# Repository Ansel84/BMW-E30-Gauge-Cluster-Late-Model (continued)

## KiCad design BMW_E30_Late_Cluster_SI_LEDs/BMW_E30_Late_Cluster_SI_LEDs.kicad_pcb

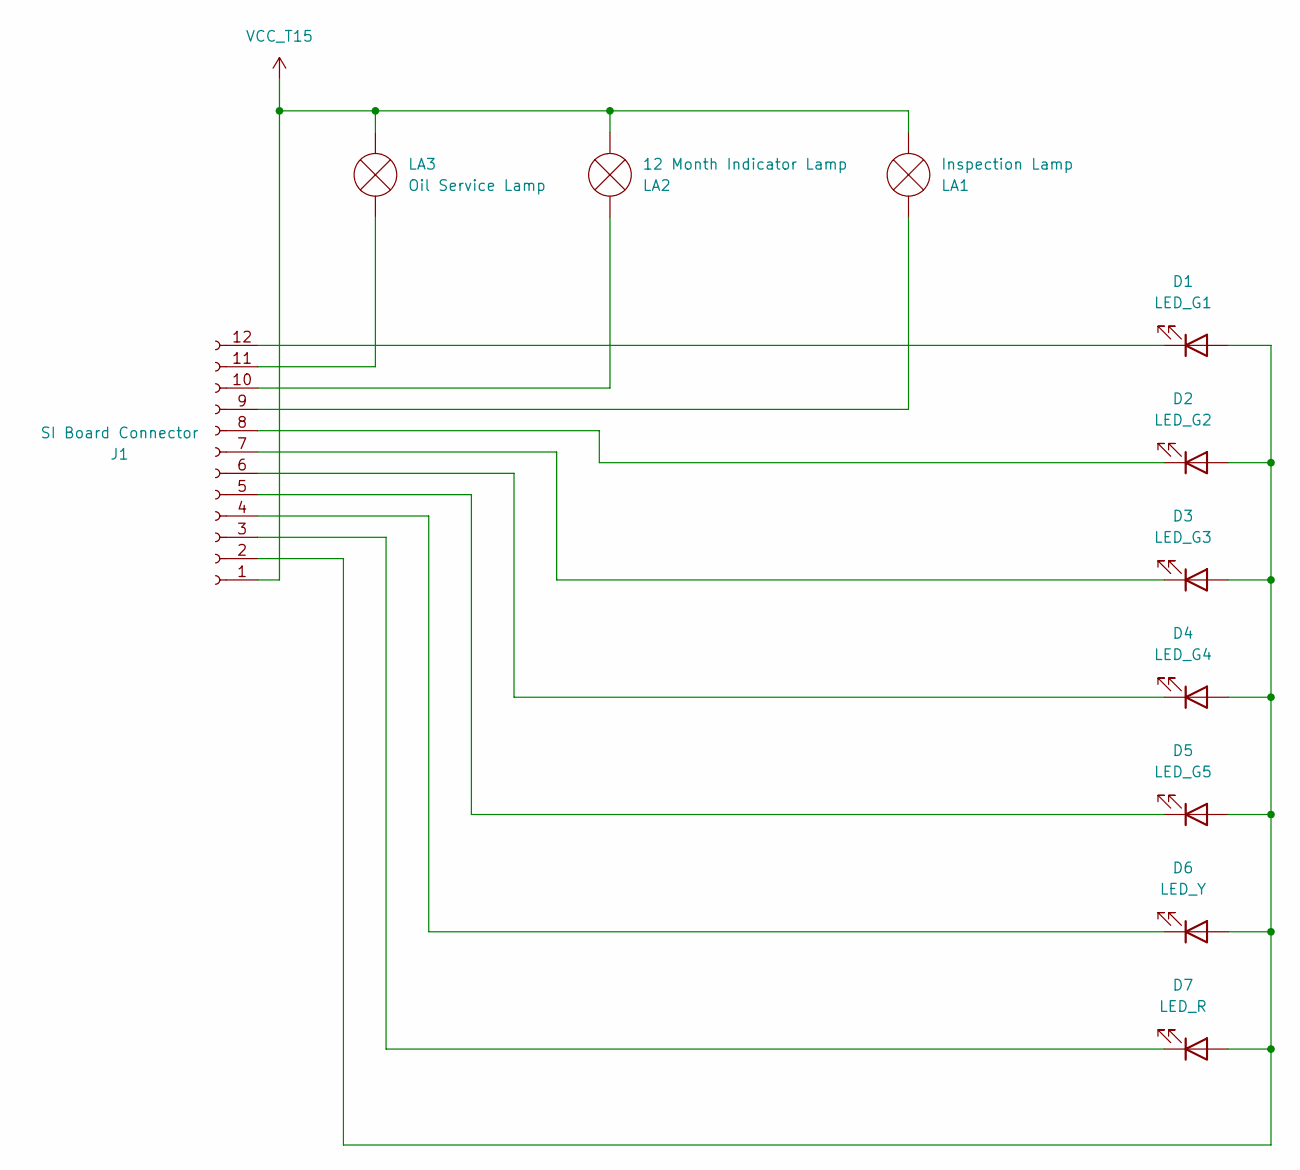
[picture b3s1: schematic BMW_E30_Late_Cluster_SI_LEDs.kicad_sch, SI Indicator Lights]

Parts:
D1: LED_G1; LED_D3.0mm
D2: LED_G2; LED_D3.0mm
D3: LED_G3; LED_D3.0mm
D4: LED_G4; LED_D3.0mm
D5: LED_G5; LED_D3.0mm
D6: LED_Y; LED_D3.0mm
D7: LED_R; LED_D3.0mm
J1: SI Board Connector; PinSocket_1x12_P2.54mm_Horizontal
LA1: Inspection Lamp; Lamp_D4.0mm_Horizontal_O3.81mm_Z2.0mm
LA2: 12 Month Indicator Lamp; Lamp_D4.0mm_Horizontal_O3.81mm_Z2.0mm
LA3: Oil Service Lamp; Lamp_D4.0mm_Horizontal_O3.81mm_Z2.0mm

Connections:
unnamed: D1.2 (A), D2.2 (A), D3.2 (A), D4.2 (A), D5.2 (A), D6.2 (A), D7.2 (A), J1.2
unnamed: D1.1 (K), J1.12
unnamed: D2.1 (K), J1.8
unnamed: D3.1 (K), J1.7
unnamed: D4.1 (K), J1.6
unnamed: D5.1 (K), J1.5
unnamed: D6.1 (K), J1.4
unnamed: D7.1 (K), J1.3
unnamed: J1.9, LA1.1 (-)
unnamed: J1.10, LA2.1 (-)
unnamed: J1.11, LA3.2 (+)
VCC_T15: J1.1, LA1.2 (+), LA2.2 (+), LA3.1 (-)

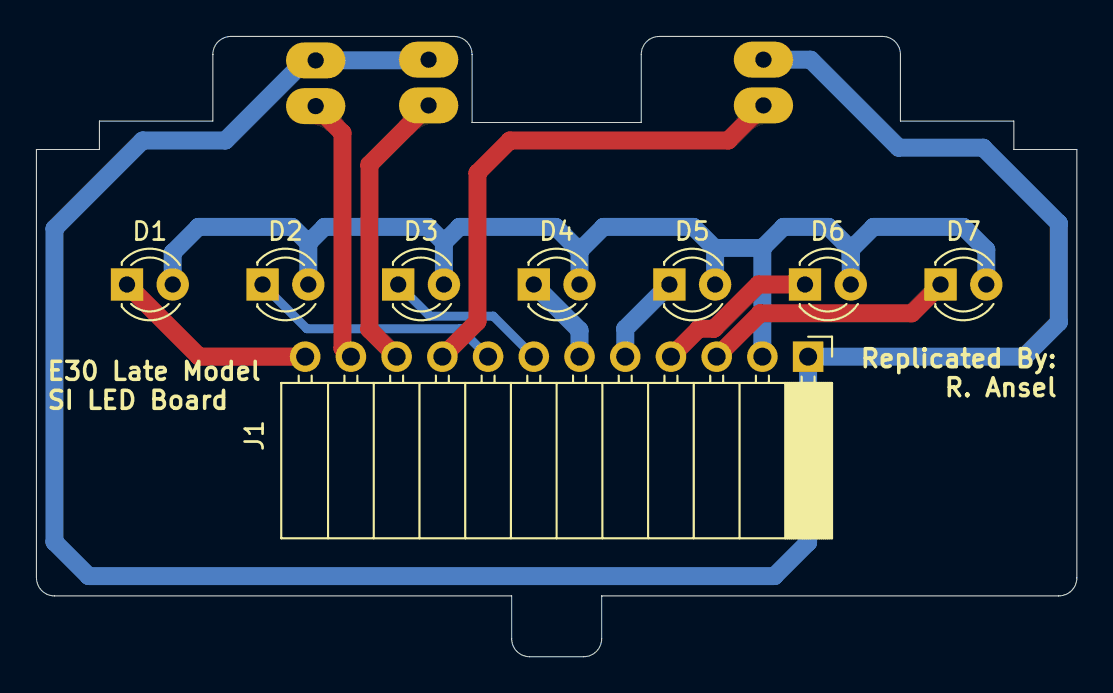
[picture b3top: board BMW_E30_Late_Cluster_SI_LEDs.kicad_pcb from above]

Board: 2 copper layers, 57.8 x 34.5 mm, 11 parts (0 on the bottom side), 12 nets.

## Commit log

2025-08-09 Add KiCad project files
2025-08-11 Create SI board project
2025-08-11 Adjust Directory Order
2025-11-02 Updates to Nexus Schematic
    C1 - C4 have all pins named. Break wear circuit completed.
2025-11-02 Nexus Schematic Complete Rough
    All connectors are pinned and labeled. Should likely do a double check to verify everything is good and then layout can begin.
2025-11-03 All Footprints Added to Nexus
    All footprints have been added to the nexus board project. Next step is to import them to the layout.
2025-11-03 Fixed Library to be project specific
    connector library was originally global which was messing with other projects, changed to local for now (might consolidate this later depending on how I want it to work.
2025-11-03 Fix Outdated Connector IV Hole Sizes
2025-11-08 Nexus Layout Updates
    Layout is about 50% complete. Need to verify exact component locations with early model board.
2025-11-08 Nexus Trace Layout Completed
    Trace layout is complete. Still need to verify some component locations
2025-11-08 Rotate Right Illum Bulb
    Changed orientation of the right side illumination bulb
2025-11-09 Standardized Board Location In Editor
    Made the board location the same in both projects so component locations can be corrected from sample runs of the early boards.
2025-11-10 Layout Updates to Match Early
    Changed a few light bulb component locations to match the correct locations on the early model boards.
2025-11-11 Added Project Files + Updates
    Added project files for SI LED daughter board and speedometer board. Started on reverse engineering schematic for late model SI board.
    Also updated some formatting on the nexus board schematic.
2025-11-12 Started SI Schematic
2025-11-13 Board Updates
    Added a few components + footprints.
    Also added custom Connector V footprint, ported from Fabian Gmeiner's early model SI board project.
2025-11-14 Update to Schematic
    Added Capacitor C13
2025-11-15 Schematic updates
    Added all capacitors
2025-11-16 Schematic Updates to SI board
    Added more resistors and diodes. Only resistors and diodes remain to be entered.
2025-11-17 updates to SI schematic
    Added several more resistors and diodes to the SI schematic.
2025-11-17 Exported PDF of Nexus Schematic
    New folder created for all schematic pdf's
2025-11-18 Update SI Schematic
    Added all of the components except for the 4 IC's. Those will require custom footprints as the chips are NLA with no datasheets.
2025-11-20 Started with Schematic Diagram
2025-11-20 Update SI Schematic
2025-11-21 Updates to SI Schematic Layout
2025-11-22 Updates to SI Schematic
2025-11-22 Schematic Progress
    All components other than IC's are accounted for in the schematic. There are still IC1 - IC4 that need custom symbols and will have a few more traces in between pins than are currently shown in the s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
2025-11-24 IC's Added to Schematic
    IC's added, started going through IC2 (U2), pinouts not complete for these yet as many pins go between chips with no other components involved.
2025-11-24 Schematic Functionally Complete
    Only changes that should need to be made are formatting and style changes to improve readability.
2025-11-25 Improved Schematic Readability for SI Board
    Added final trace flags for readability of the main page. Also exported a BOM for the SI board
2025-11-27 Completed Schematic + Layout for SI LED
    Additional labels were added to the SI board schematic to denote which pin controls which light on the LED board.
2025-11-28 SI Board Cuts
2025-11-28 Update LICENSE
2025-12-01 SI layout updates
    Component positions are mostly complete.
2025-12-02 Component Locations Generally Set
    Component locations set up and ready for layout to begin.
2025-12-03 SI Board Layout Updates
2025-12-05 SI Board Layout Updates
    Continued updating traces from the coding plug side of the board.
2025-12-07 SI Board Layout Complete
2025-12-07 Readability Improvements
    Organized the schematic for better readability, also made a few minor adjustments to the layout for simplicity.
2025-12-10 Board Styling on SI and SI LED
    Added fillets to the SI and SI_LED boards and generated the first gbr files for pricing estimation on JLC.
2025-12-18 Updates for GBR files
    Slight stylistic improvements for GBR files as well as added some links to parts on digikey.
2025-12-22 Stylistic Edits for Readability
2025-12-31 Change location of Coding Plug Connector
    Updated coding plug connector to be lower so that it interfaces with the coding plug better.
2026-01-01 Layout Update + Schematic Style
    Widened a problematic cutout in the layout for V2 of the board. Also made small stylistic improvements to Schematic.
2026-01-01 Layout Adjustment
2026-01-11 Updated Resistor Value
    R28 Value was incorrect, changed from 200R to 200k ohms
2026-01-11 Fixed Error in edge cut layer
2026-01-19 Update Connector V
    Change Connector V to an updated version that is more accurate to the original pins. Note that depending on Early model updates and subsequent board runs, the outline may have to be moved up by 0.2 m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
2026-01-31 Updated R2 Specs
2026-02-19 Moved C17 for readability
2026-02-19 Add SMD Provisions
    Added SMD mount options for C12, C4, and C2 so that axial lead electrolytics are not necessary to purchase from the BOM.
2026-02-21 Added footprint for SI light connector
2026-02-22 Layout Fitment Changes
    Widened both bottom slots of the board size. Also shifted J5 and J1 to match the original board better. Anchor point is the coding plug insert. This offsets the original anchor point of the left boar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
2026-02-22 Layout fixes
    Some traces were not connected.
2026-02-22 Layout Updates
    Moved battery footprints to closer match the original. Also moved the groupings of resistors in the center lower section of the board to be further away from the board edge for better fitment.
2026-02-22 Cleaned up fab layers
    moved fab labels for readability when printouts are generated for component location reference documentation.
2026-02-23 Notation Update + BOM
    Installed JLC's fabrication plugin and generated a BOM as well as gbr files in the "production" folder.
2026-03-04 Update Silkscreen
2026-03-14 Update Nexus Schematic pdf
2026-03-16 Added Reans logo
2026-03-22 Silkscreen updates
    Updated silkscreen to include website and company name.
2026-03-24 Updated gerber zip
2026-05-04 Update Fill Pattern
2026-05-25 Add Note to SI schematic
2026-05-26 Update SI Schematic R19 Notation
2026-06-03 Update Schematic PDFs
    Added updates to schematic pdf documents for consistency
2026-06-03 Layout Updates to SI board
2026-06-06 Update schematic
    Change "battery charging" to "Memory Battery Backup" to reflect how the circuit works
